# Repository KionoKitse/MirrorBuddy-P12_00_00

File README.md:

### Description 
A project to automate power mirrors. The system will detect who is driving based on their seat position. From this, the system will automatically adjust the mirror position based on the detected user's known preferences. Additionally the system will be able to learn new settings if a user has decided to manually adjust the mirror position. 

### Hardware in use
* 1X ATmega328 (Arduino Pro Mini)
* 1X YX-X801 (low voltage cutoff)
* 2X ATtiny85 (micro processor)
* 3X L7805CV (voltage regulator)
* 4X OH137 (hall Sensor)
* 3X MAX485 (RS485 communication modules)

### What's next
* Get ATTiny85 to send a number via RS485 and display it on Arduino with OLED
* Get ATTiny85 to send the values in the correct format
* Design circuit boards  
 
### Progress log 
<details>
	<summary>Details of the project history</summary>
	
* 2021-10-05 Started the GitHub repository
* 2021-10-06 OLED test with Pro Mini
* 2021-10-07 Tested transmitting a value from ATtiny85 to ATmega328 over RS485 and displayed with OLED
* 2021-10-13 Building a RS485 HAT to ease testing
* 2021-10-18 Got the plotter working
* 2021-10-18 Monitor hall over serial working fine
* 2022-10-09 Hall sensor reading from spare housing
* 2022-10-10 Working on code to count number of rotations
* 2022-10-10 ATtiny with peakdetection and softserial
* 2022-10-11 Determined that peak detection uses too much memory "Global variables use 489 bytes (95%) of dynamic memory"
* 2022-10-12 Created a simpler peak detection algorithm 
* 2022-10-13 Added a debounce setting to MonitorHall it seems to be sending counts as expected 
* 2022-10-14 Added code to monitor 2 hall sensors 
* 2022-10-16 Built a relay board that can control the motors 
* 2022-10-17 Working on code to control relay board
* 2022-10-24 Soldered the relay board into the wiring harness
* 2022-10-24 There is some issue with the relay board everything shorts to ground when adjusting the switch
* 2022-10-25 Added a KiCad model to the project
</details>

### Notebook
<details>
	<summary>Next steps</summary>
	
* Voltage divider to sense mirror controls
* Test inputs from mirror switch
* Check for noise with 5V regulator on bench
* Check voltage stability in the car with regulator
* Check if we can run without voltage regulators on each mirror
* ProMini turn on motors then turn off after correct number of rotations achieved 
* Test with multiple MAX485 modules on the network
* Build sample module with ATTiny85
</details>

<details>
	<summary>Notes on the project</summary>
	
* Best to have ATTiny85 keep track of count in case ATmega328 misses a count
* Would be nice to see the actual values that got triggered for data monitoring
* RS485 only send a byte so that makes it challenging for sending an int
* Plotting with RS485 seems too slow
* Would be interesting to see if the MAX485 module could do TX/RX might make calibration easier
* Does rail voltage affect the hall sensors? If so then maybe it would be good to only calibrate them after the voltage has stabilized. 
</details>

<details>
	<summary>Overview</summary>
	
- ProMini is the controller
	* It will detect which diver is in the seat
	* It will detect if the driver has adjusted the mirror
	* It will activate the controls to adjust the mirrors to the correct place
	* Data received
		+ The proMini will be receiving a value that is between 0-255 that contains the limit data and count
		+ It will know which ATtiney is sending because it will be controlling the power to the mirrors
		+ It will also know who is sending because it will have a sensor to detect which way the mirror button is pointing if the user is manually adjusting the mirror position
		+ In the case that the magnet stops in front of the hall sensor then the ATtiny will be sending sporadic readings
		+ There will need to be some sort of way to filter out this noise or adjust the mirrors a little bit to avoid this
- ATtiny85 1&2 are the sensors that monitor the position of the mirrors
	* They will send a signal when the limit switches have been activated
	* They will sens a signal when the hall sensors have detected the magnet passing
	* The RS485 sends a byte of data so that 0-255
	* Data sent
		+ 100 is limit switch for sensor 1 is hit
		+ 200 is limit switch for sensor 2 is hit
		+ 150 is 50 rotations on sensor 1 counted
		+ 255 is 55 rotations counted on sensor 2
	* The count on sensors is reset after 2 seconds of not seeing the hall sensor move
	* There should be some way to calibrate the threshold for the hall sensor reading
	* When it gets power (car turned on) the ProMini will move the mirrors to their outer limits
	* While this is happening the ATtiny85 will be recording the values detected
	* The ProMini will stop and wait a few seconds
	* When the ATtiny detects that it hasn't moved in a while it will use a filter on the collected data to determine the cutoff threshold
	* This data will be sent to the ProMini for logging and the threshold will be set
	* After this data has been sent the ProMini will know that it is okay to move the mirrors into possition
</details>

<details>
	<summary>Collision avoidance</summary>
	
- Collisions are avoided because the ProMini will only be controlling one ATtiny85 at a time so only one node will be transmitting at a time
- It would be impossible for both nodes to be transmitting since the user can only move one mirror at a time
</details>

<details>
	<summary>General thoughts</summary>
	
- Having the ProMini being the controller will allow me to make fine adjustments without having to pull the mirrors off
- limit switches
	* It could be problematic to use the limit switches since they could easily get water damaged since they are exposed to the elements quite a lot. It would be beneficial not not have to rely on them.
	* If I was doing this again I would not have added them since I could easily drive the motors out until I'm sure I'm at the outside limit and then work backwards from there.
	* The inside limit puts stress on the plastic nuts but the outside limit does not
	* Perhaps it's better to not use the limits at all
</details>

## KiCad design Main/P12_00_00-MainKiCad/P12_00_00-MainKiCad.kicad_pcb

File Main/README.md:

### Description 
In this test the ATTiny85 reads the value of the potentiometer and converts it to a value between 1-180. Then it passes this value over the software serial to the MAX485. A MAX485 on the other side gets the number and sends it to at ATmega328p which displays the value on an SPI OLED screen.

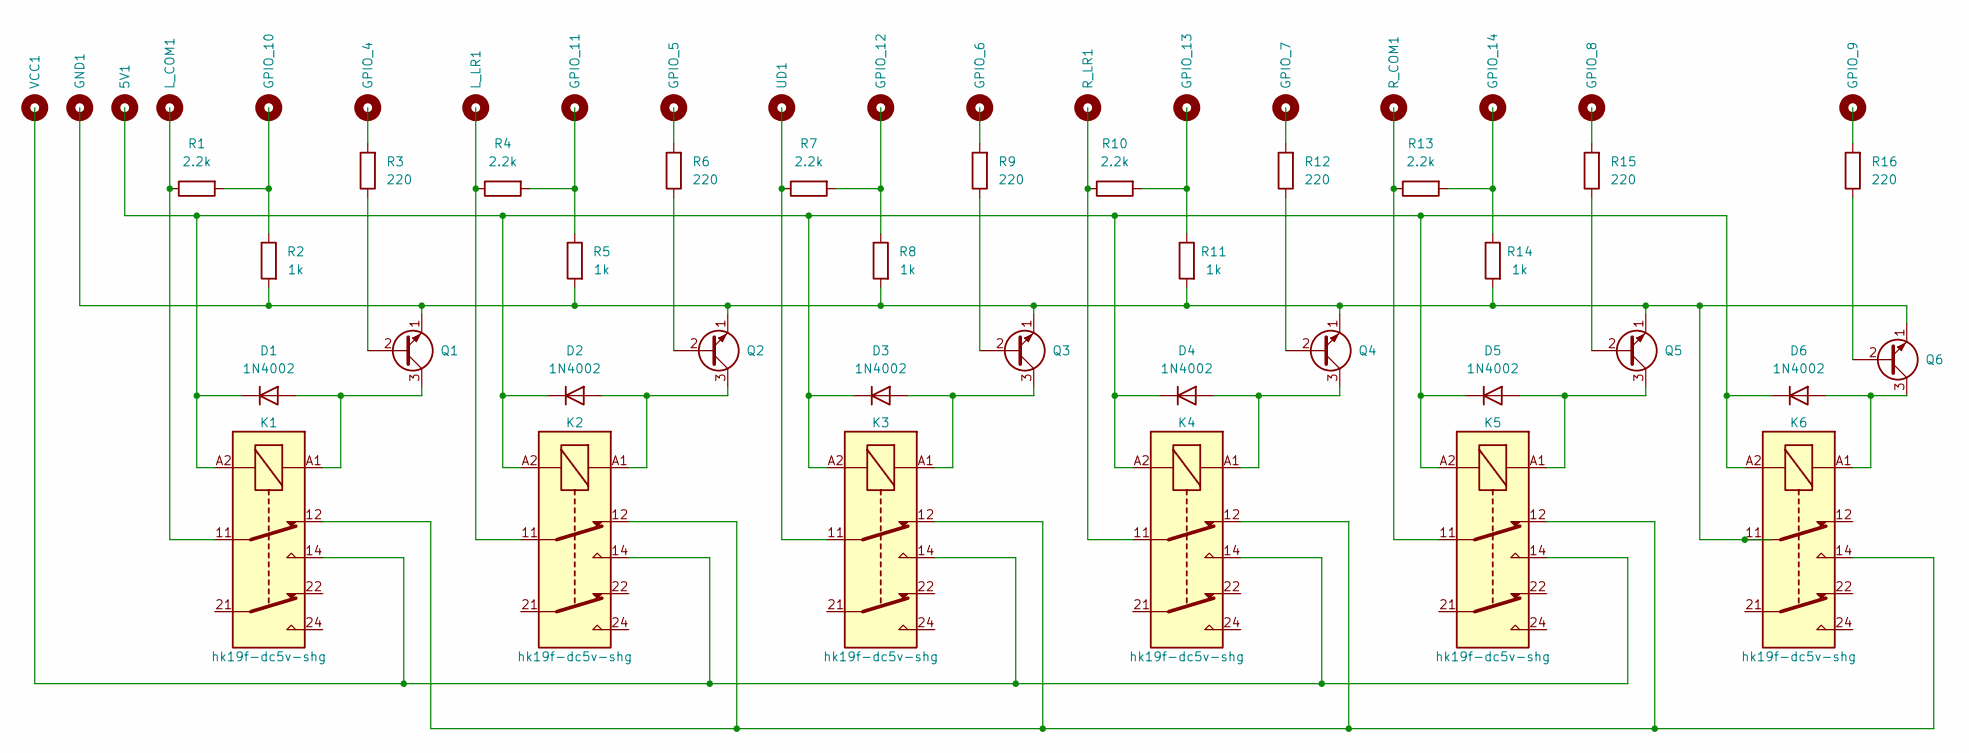
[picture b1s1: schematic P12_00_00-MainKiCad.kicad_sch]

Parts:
5V1: L_COM; MountingHole_2.1mm
D1, D2, D3, D4, D5, D6: 1N4002; D_DO-34_SOD68_P7.62mm_Horizontal
GND1: L_COM; MountingHole_2.1mm
GPIO_4, GPIO_5, GPIO_6, GPIO_7, GPIO_8, GPIO_9, GPIO_10, GPIO_11, GPIO_12, GPIO_13, GPIO_14: L_COM; MountingHole_2.1mm
K1, K2, K3, K4, K5, K6: hk19f-dc5v-shg; Relay_DPDT_Schrack-RT2-FormC_RM5mm
L_COM1: L_COM; MountingHole_2.1mm
L_LR1: L_COM; MountingHole_2.1mm
Q1, Q2, Q3, Q4, Q5, Q6: 2N3904; TO-92_Inline
R1, R4, R7, R10, R13: 2.2k; R_Axial_DIN0204_L3.6mm_D1.6mm_P5.08mm_Horizontal
R2, R5, R8, R11, R14: 1k; R_Axial_DIN0204_L3.6mm_D1.6mm_P5.08mm_Horizontal
R3, R6, R9, R12, R15, R16: 220; R_Axial_DIN0204_L3.6mm_D1.6mm_P5.08mm_Horizontal
R_COM1: L_COM; MountingHole_2.1mm
R_LR1: L_COM; MountingHole_2.1mm
UD1: L_COM; MountingHole_2.1mm
VCC1: L_COM; MountingHole_2.1mm

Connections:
unnamed: D1.1 (K), D2.1 (K), D3.1 (K), D4.1 (K), D5.1 (K), D6.1 (K), K1.A2, K2.A2, K3.A2, K4.A2, K5.A2, K6.A2
unnamed: D1.2 (A), K1.A1, Q1.3 (C)
unnamed: K1.11, R1.1
unnamed: K1.12, K2.12, K3.12, K4.12, K5.12, K6.14
unnamed: K1.14, K2.14, K3.14, K4.14, K5.14
unnamed: D2.2 (A), K2.A1, Q2.3 (C)
unnamed: D3.2 (A), K3.A1, Q3.3 (C)
unnamed: D4.2 (A), K4.A1, Q4.3 (C)
unnamed: D5.2 (A), K5.A1, Q5.3 (C)
unnamed: D6.2 (A), K6.A1, Q6.3 (C)
unnamed: K6.11, Q1.1 (E), Q2.1 (E), Q3.1 (E), Q4.1 (E), Q5.1 (E), Q6.1 (E), R2.2, R5.2, R8.2, R11.2, R14.2
unnamed: Q1.2 (B), R3.1
unnamed: Q6.2 (B), R16.1
unnamed: R1.2, R2.1
unnamed: K2.11, R4.1
unnamed: R4.2, R5.1
unnamed: Q2.2 (B), R6.1
unnamed: K3.11, R7.1
unnamed: R7.2, R8.1
unnamed: Q3.2 (B), R9.1
unnamed: K4.11, R10.1
unnamed: R10.2, R11.1
unnamed: Q4.2 (B), R12.1
unnamed: K5.11, R13.1
unnamed: R13.2, R14.1
unnamed: Q5.2 (B), R15.1

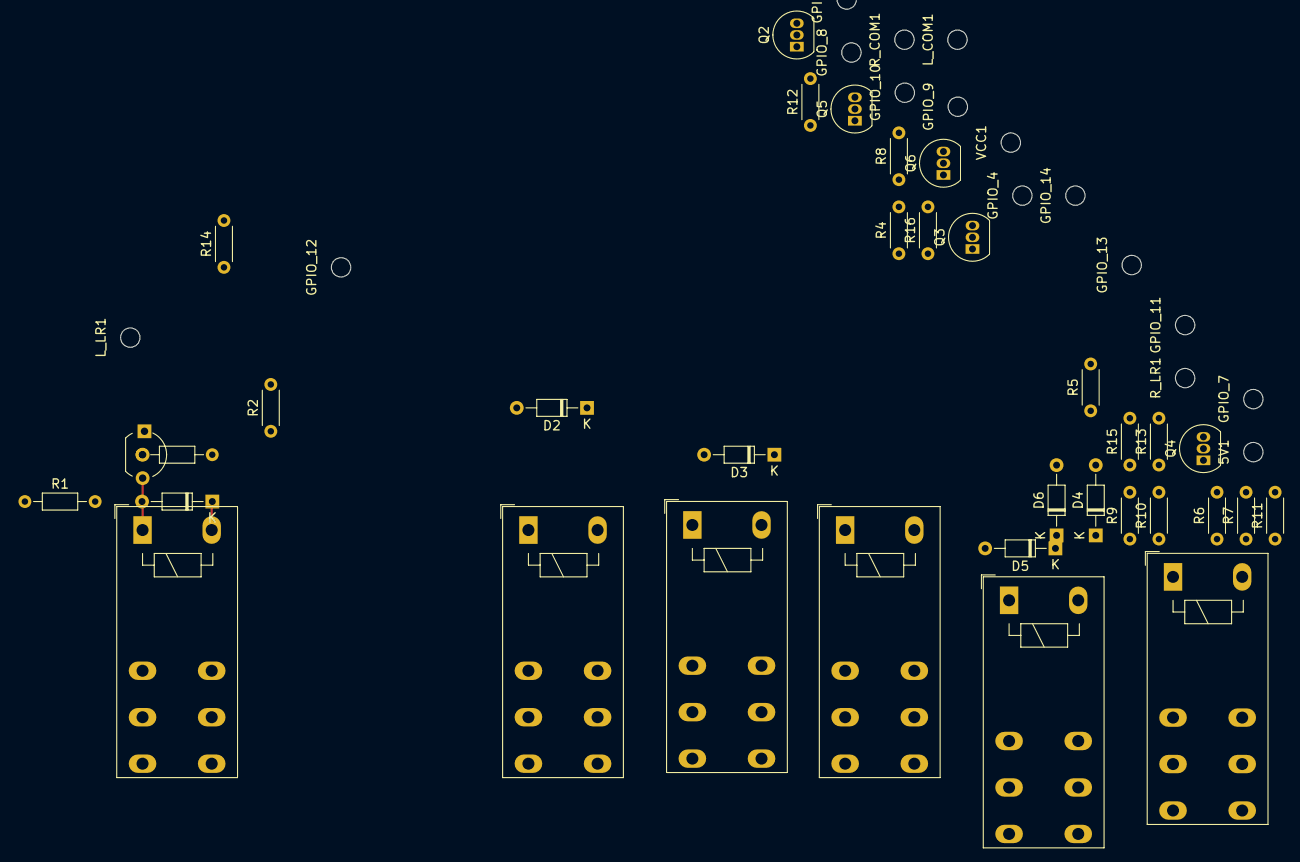
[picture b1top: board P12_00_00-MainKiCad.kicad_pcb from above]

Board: 2 copper layers, 53 parts (0 on the bottom side), 26 nets.

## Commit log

2021-10-07 OLED test
2021-10-07 RS485-Simple
2021-10-07 Save point PlotHall
2021-10-13 Working to send int over RS485
2021-10-13 Working on main circuit
2021-10-18 Got the plotter working
2021-10-18 Main circuit
2021-10-18 Monitor Hall Sketch
2021-10-26 Working on Main
2021-11-26 none
2022-09-26 Test program for ATtiny85 module
2022-10-11 Working on peak detection with ATtiny85 and MAX485
    Peak detection and max485 aren't working together I suspect that I'm running out of memory so I might need a different peak detection or soft serial
2022-10-11 Working on getting peak detection to work
2022-10-12 Created a simpler peak detection algorithm
2022-10-13 Added a debounce setting to MonitorHall
2022-10-14 Added code to monitor 2 hall sensors
2022-10-17 Working on motor controller
2022-10-17 Code to support the relay board
2022-10-24 Working on main program
2022-10-25 Added a KiCad model to the project
2022-10-26 KiCAD modifications
2022-10-31 Working with the schematic
